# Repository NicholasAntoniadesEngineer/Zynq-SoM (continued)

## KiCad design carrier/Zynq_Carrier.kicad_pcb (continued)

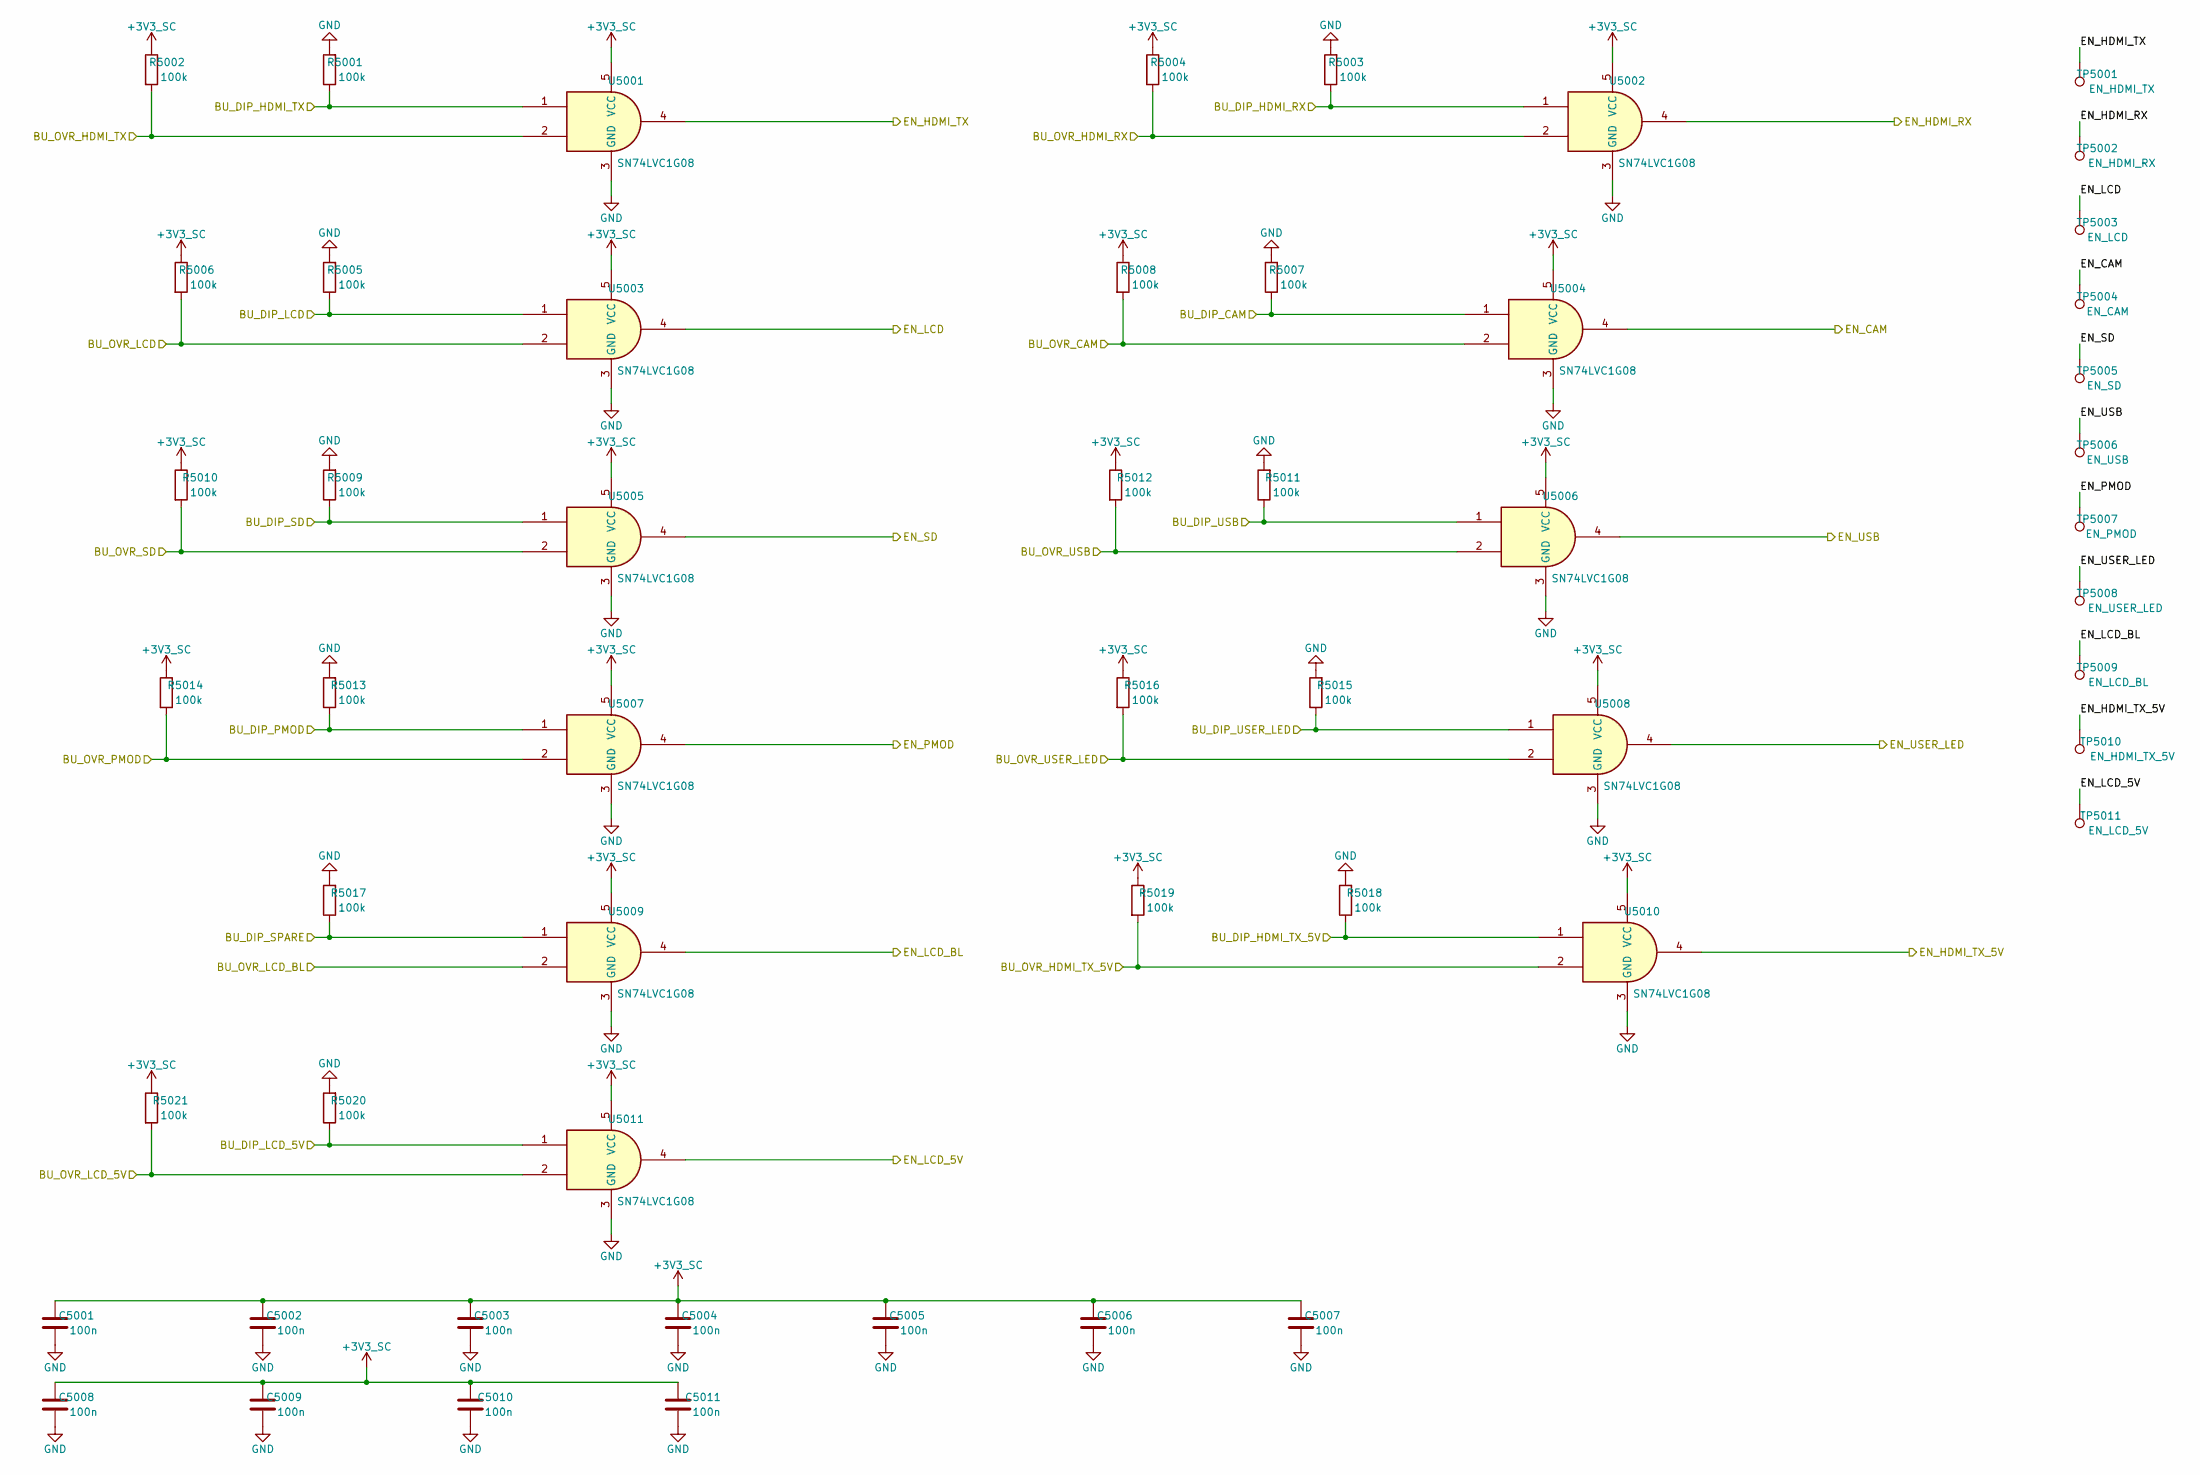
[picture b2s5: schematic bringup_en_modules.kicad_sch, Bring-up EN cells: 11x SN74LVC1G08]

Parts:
C5001, C5002, C5003, C5004, C5005, C5006, C5007, C5008, C5009, C5010, C5011: 100n; C_0603_1608Metric; LCSC C14663
R5001, R5002, R5003, R5004, R5005, R5006, R5007, R5008, R5009, R5010, R5011, R5012, R5013, R5014, R5015, R5016, R5017, R5018, R5019, R5020, R5021: 100k; R_0603_1608Metric; LCSC C25803
TP5001: EN_HDMI_TX; TestPoint_Pad_D1.5mm
TP5002: EN_HDMI_RX; TestPoint_Pad_D1.5mm
TP5003: EN_LCD; TestPoint_Pad_D1.5mm
TP5004: EN_CAM; TestPoint_Pad_D1.5mm
TP5005: EN_SD; TestPoint_Pad_D1.5mm
TP5006: EN_USB; TestPoint_Pad_D1.5mm
TP5007: EN_PMOD; TestPoint_Pad_D1.5mm
TP5008: EN_USER_LED; TestPoint_Pad_D1.5mm
TP5009: EN_LCD_BL; TestPoint_Pad_D1.5mm
TP5010: EN_HDMI_TX_5V; TestPoint_Pad_D1.5mm
TP5011: EN_LCD_5V; TestPoint_Pad_D1.5mm
U5001, U5002, U5003, U5004, U5005, U5006, U5007, U5008, U5009, U5010, U5011: SN74LVC1G08; SOT-23-5; LCSC C7666

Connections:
+3V3_SC: C5001.1, C5002.1, C5003.1, C5004.1, C5005.1, C5006.1, C5007.1, C5008.1, C5009.1, C5010.1, C5011.1, R5002.1, R5004.1, R5006.1, R5008.1, R5010.1, R5012.1, R5014.1, R5016.1, R5019.1, R5021.1, U5001.5 (VCC), U5002.5 (VCC), U5003.5 (VCC), U5004.5 (VCC), U5005.5 (VCC), U5006.5 (VCC), U5007.5 (VCC), U5008.5 (VCC), U5009.5 (VCC), U5010.5 (VCC), U5011.5 (VCC); also elsewhere on the board
BU_DIP_CAM: R5007.1, U5004.1; also elsewhere on the board
BU_DIP_HDMI_RX: R5003.1, U5002.1; also elsewhere on the board
BU_DIP_HDMI_TX: R5001.1, U5001.1; also elsewhere on the board
BU_DIP_HDMI_TX_5V: R5018.1, U5010.1; also elsewhere on the board
BU_DIP_LCD: R5005.1, U5003.1; also elsewhere on the board
BU_DIP_LCD_5V: R5020.1, U5011.1; also elsewhere on the board
BU_DIP_PMOD: R5013.1, U5007.1; also elsewhere on the board
BU_DIP_SD: R5009.1, U5005.1; also elsewhere on the board
BU_DIP_SPARE: R5017.1, U5009.1; also elsewhere on the board
BU_DIP_USB: R5011.1, U5006.1; also elsewhere on the board
BU_DIP_USER_LED: R5015.1, U5008.1; also elsewhere on the board
BU_OVR_CAM: R5008.2, U5004.2; also elsewhere on the board
BU_OVR_HDMI_RX: R5004.2, U5002.2; also elsewhere on the board
BU_OVR_HDMI_TX: R5002.2, U5001.2; also elsewhere on the board
BU_OVR_HDMI_TX_5V: R5019.2, U5010.2; also elsewhere on the board
BU_OVR_LCD: R5006.2, U5003.2; also elsewhere on the board
BU_OVR_LCD_5V: R5021.2, U5011.2; also elsewhere on the board
BU_OVR_LCD_BL: U5009.2; also elsewhere on the board
BU_OVR_PMOD: R5014.2, U5007.2; also elsewhere on the board
BU_OVR_SD: R5010.2, U5005.2; also elsewhere on the board
BU_OVR_USB: R5012.2, U5006.2; also elsewhere on the board
BU_OVR_USER_LED: R5016.2, U5008.2; also elsewhere on the board
EN_CAM: TP5004.1, U5004.4; also elsewhere on the board
EN_HDMI_RX: TP5002.1, U5002.4; also elsewhere on the board
EN_HDMI_TX: TP5001.1, U5001.4; also elsewhere on the board
EN_HDMI_TX_5V: TP5010.1, U5010.4; also elsewhere on the board
EN_LCD: TP5003.1, U5003.4; also elsewhere on the board
EN_LCD_5V: TP5011.1, U5011.4; also elsewhere on the board
EN_LCD_BL: TP5009.1, U5009.4
EN_PMOD: TP5007.1, U5007.4; also elsewhere on the board
EN_SD: TP5005.1, U5005.4; also elsewhere on the board
EN_USB: TP5006.1, U5006.4; also elsewhere on the board
EN_USER_LED: TP5008.1, U5008.4; also elsewhere on the board
GND: C5001.2, C5002.2, C5003.2, C5004.2, C5005.2, C5006.2, C5007.2, C5008.2, C5009.2, C5010.2, C5011.2, R5001.2, R5003.2, R5005.2, R5007.2, R5009.2, R5011.2, R5013.2, R5015.2, R5017.2, R5018.2, R5020.2, U5001.3 (GND), U5002.3 (GND), U5003.3 (GND), U5004.3 (GND), U5005.3 (GND), U5006.3 (GND), U5007.3 (GND), U5008.3 (GND), U5009.3 (GND), U5010.3 (GND), U5011.3 (GND); also elsewhere on the board

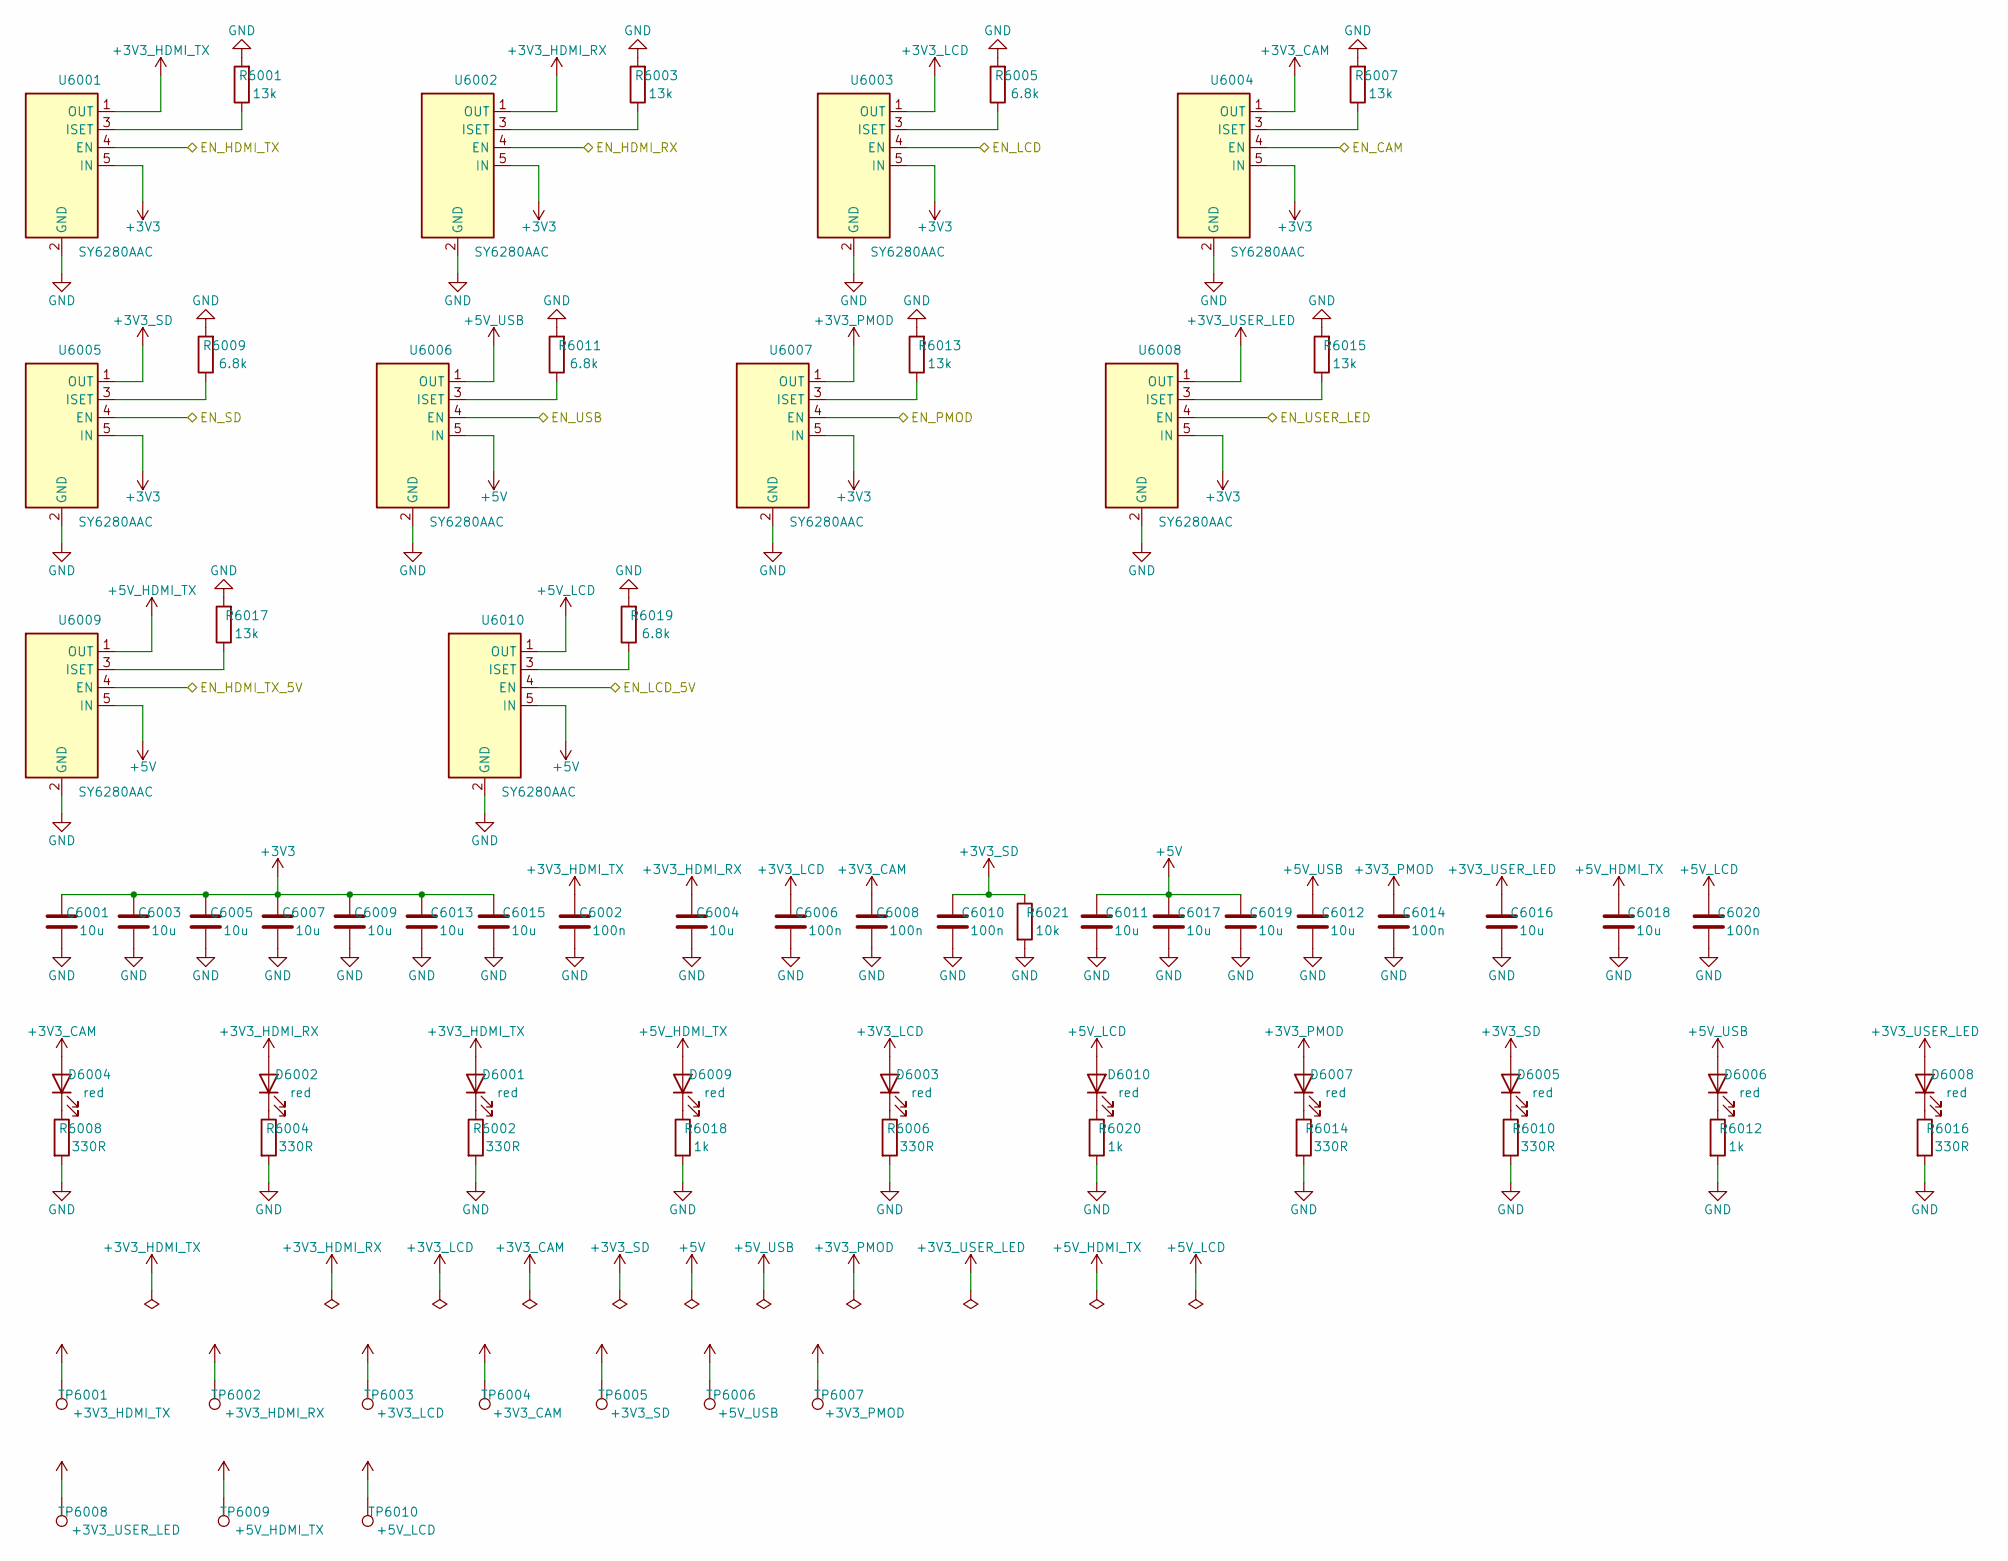
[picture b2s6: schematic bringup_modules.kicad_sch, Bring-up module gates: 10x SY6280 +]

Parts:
C6001, C6003, C6004, C6005, C6007, C6009, C6011, C6012, C6013, C6015, C6016, C6017, C6018, C6019: 10u; C_0805_2012Metric; LCSC C15850
C6002, C6006, C6008, C6010, C6014, C6020: 100n; C_0603_1608Metric; LCSC C14663
D6001, D6002, D6003, D6004, D6005, D6006, D6007, D6008, D6009, D6010: red; LED_0603_1608Metric; LCSC C2286
R6001, R6003, R6007, R6013, R6015, R6017: 13k; R_0603_1608Metric; LCSC C22797
R6002, R6004, R6006, R6008, R6010, R6014, R6016: 330R; R_0603_1608Metric; LCSC C23138
R6005, R6009, R6011, R6019: 6.8k; R_0603_1608Metric; LCSC C23212
R6012, R6018, R6020: 1k; R_0603_1608Metric; LCSC C21190
R6021: 10k; R_0603_1608Metric; LCSC C25804
TP6001: +3V3_HDMI_TX; TestPoint_Pad_D1.5mm
TP6002: +3V3_HDMI_RX; TestPoint_Pad_D1.5mm
TP6003: +3V3_LCD; TestPoint_Pad_D1.5mm
TP6004: +3V3_CAM; TestPoint_Pad_D1.5mm
TP6005: +3V3_SD; TestPoint_Pad_D1.5mm
TP6006: +5V_USB; TestPoint_Pad_D1.5mm
TP6007: +3V3_PMOD; TestPoint_Pad_D1.5mm
TP6008: +3V3_USER_LED; TestPoint_Pad_D1.5mm
TP6009: +5V_HDMI_TX; TestPoint_Pad_D1.5mm
TP6010: +5V_LCD; TestPoint_Pad_D1.5mm
U6001, U6002, U6003, U6004, U6005, U6006, U6007, U6008, U6009, U6010: SY6280AAC; LCSC C55136

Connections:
+3V3: C6001.1, C6003.1, C6005.1, C6007.1, C6009.1, C6013.1, C6015.1, U6001.5 (IN), U6002.5 (IN), U6003.5 (IN), U6004.5 (IN), U6005.5 (IN), U6007.5 (IN), U6008.5 (IN); also elsewhere on the board
+3V3_CAM: C6008.1, D6004.2 (A), TP6004.1, U6004.1 (OUT); also elsewhere on the board
+3V3_HDMI_RX: C6004.1, D6002.2 (A), TP6002.1, U6002.1 (OUT); also elsewhere on the board
+3V3_HDMI_TX: C6002.1, D6001.2 (A), TP6001.1, U6001.1 (OUT); also elsewhere on the board
+3V3_LCD: C6006.1, D6003.2 (A), TP6003.1, U6003.1 (OUT); also elsewhere on the board
+3V3_PMOD: C6014.1, D6007.2 (A), TP6007.1, U6007.1 (OUT); also elsewhere on the board
+3V3_SD: C6010.1, D6005.2 (A), R6021.1, TP6005.1, U6005.1 (OUT); also elsewhere on the board
+3V3_USER_LED: C6016.1, D6008.2 (A), TP6008.1, U6008.1 (OUT); also elsewhere on the board
+5V: C6011.1, C6017.1, C6019.1, U6006.5 (IN), U6009.5 (IN), U6010.5 (IN); also elsewhere on the board
+5V_HDMI_TX: C6018.1, D6009.2 (A), TP6009.1, U6009.1 (OUT); also elsewhere on the board
+5V_LCD: C6020.1, D6010.2 (A), TP6010.1, U6010.1 (OUT); also elsewhere on the board
+5V_USB: C6012.1, D6006.2 (A), TP6006.1, U6006.1 (OUT); also elsewhere on the board
EN_CAM: U6004.4 (EN); also elsewhere on the board
EN_HDMI_RX: U6002.4 (EN); also elsewhere on the board
EN_HDMI_TX: U6001.4 (EN); also elsewhere on the board
EN_HDMI_TX_5V: U6009.4 (EN); also elsewhere on the board
EN_LCD: U6003.4 (EN); also elsewhere on the board
EN_LCD_5V: U6010.4 (EN); also elsewhere on the board
EN_PMOD: U6007.4 (EN); also elsewhere on the board
EN_SD: U6005.4 (EN); also elsewhere on the board
EN_USB: U6006.4 (EN); also elsewhere on the board
EN_USER_LED: U6008.4 (EN); also elsewhere on the board
GND: C6001.2, C6002.2, C6003.2, C6004.2, C6005.2, C6006.2, C6007.2, C6008.2, C6009.2, C6010.2, C6011.2, C6012.2, C6013.2, C6014.2, C6015.2, C6016.2, C6017.2, C6018.2, C6019.2, C6020.2, R6001.2, R6002.2, R6003.2, R6004.2, R6005.2, R6006.2, R6007.2, R6008.2, R6009.2, R6010.2, R6011.2, R6012.2, R6013.2, R6014.2, R6015.2, R6016.2, R6017.2, R6018.2, R6019.2, R6020.2, R6021.2, U6001.2 (GND), U6002.2 (GND), U6003.2 (GND), U6004.2 (GND), U6005.2 (GND), U6006.2 (GND), U6007.2 (GND), U6008.2 (GND), U6009.2 (GND), U6010.2 (GND); also elsewhere on the board
unnamed: D6001.1 (K), R6002.1
unnamed: D6002.1 (K), R6004.1
unnamed: D6003.1 (K), R6006.1
unnamed: D6004.1 (K), R6008.1
unnamed: D6005.1 (K), R6010.1
unnamed: D6006.1 (K), R6012.1
unnamed: D6007.1 (K), R6014.1
unnamed: D6008.1 (K), R6016.1
unnamed: D6009.1 (K), R6018.1
unnamed: D6010.1 (K), R6020.1
unnamed: R6001.1, U6001.3 (ISET)
unnamed: R6003.1, U6002.3 (ISET)
unnamed: R6005.1, U6003.3 (ISET)
unnamed: R6007.1, U6004.3 (ISET)
unnamed: R6009.1, U6005.3 (ISET)
unnamed: R6011.1, U6006.3 (ISET)
unnamed: R6013.1, U6007.3 (ISET)
unnamed: R6015.1, U6008.3 (ISET)
unnamed: R6017.1, U6009.3 (ISET)
unnamed: R6019.1, U6010.3 (ISET)

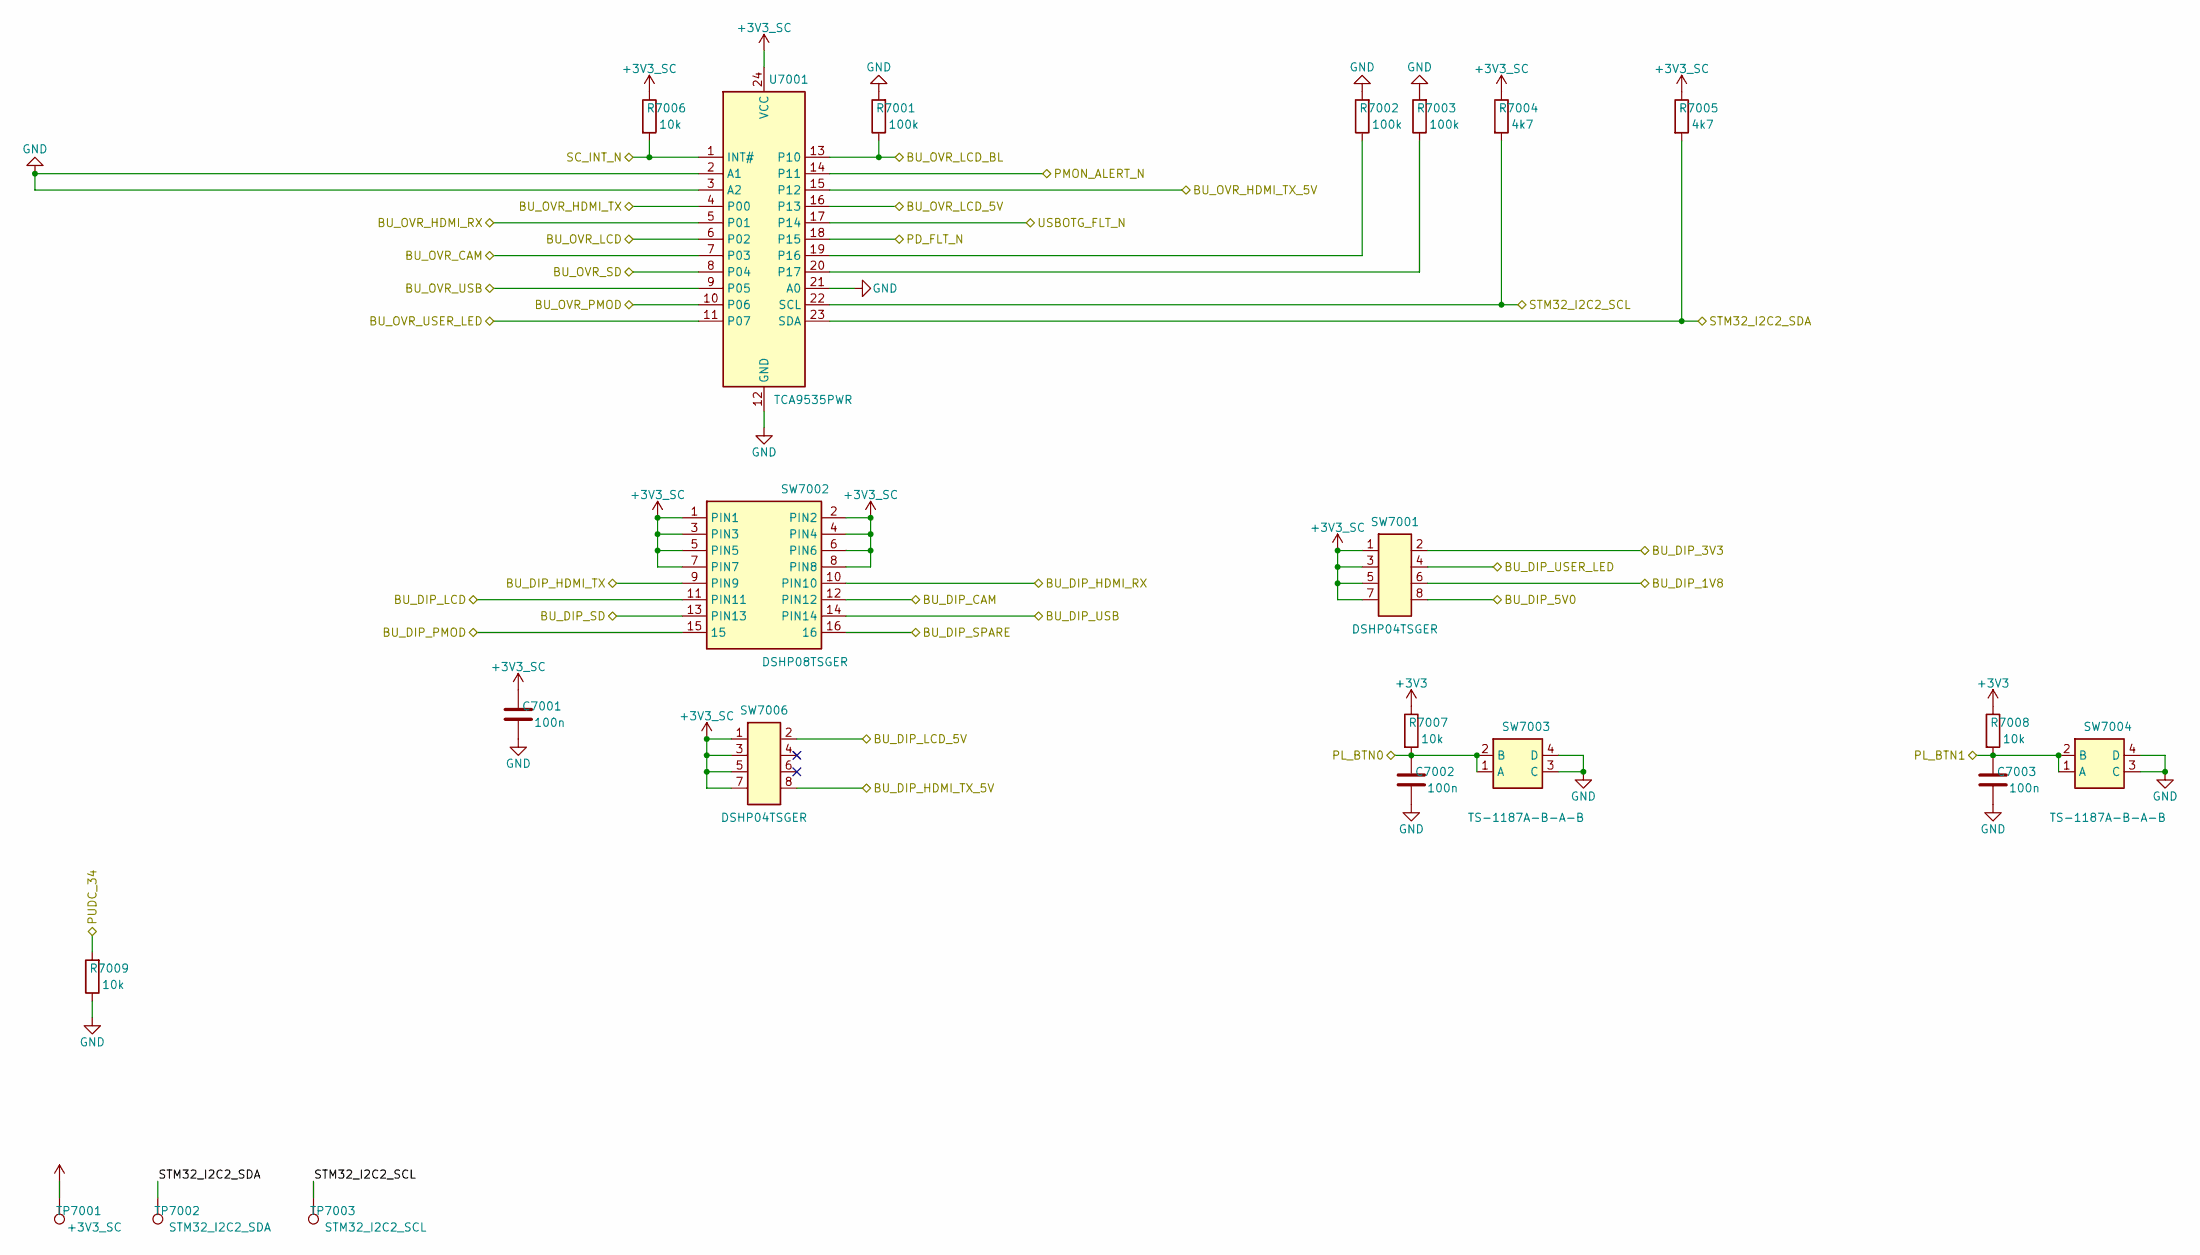
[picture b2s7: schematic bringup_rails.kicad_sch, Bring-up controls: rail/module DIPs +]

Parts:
C7001, C7002, C7003: 100n; C_0603_1608Metric; LCSC C14663
R7001, R7002, R7003: 100k; R_0603_1608Metric; LCSC C25803
R7004, R7005: 4k7; R_0603_1608Metric; LCSC C23162
R7006, R7007, R7008, R7009: 10k; R_0603_1608Metric; LCSC C25804
SW7001, SW7006: DSHP04TSGER; LCSC C3293144
SW7002: DSHP08TSGER; LCSC C3293147
SW7003, SW7004: TS-1187A-B-A-B; LCSC C318884
TP7001: +3V3_SC; TestPoint_Pad_D1.5mm
TP7002: STM32_I2C2_SDA; TestPoint_Pad_D1.5mm
TP7003: STM32_I2C2_SCL; TestPoint_Pad_D1.5mm
U7001: TCA9535PWR; LCSC C130204

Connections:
+3V3: R7007.1, R7008.1; also elsewhere on the board
+3V3_SC: C7001.1, R7004.1, R7005.1, R7006.1, SW7001.1, SW7001.3, SW7001.5, SW7001.7, SW7002.1 (PIN1), SW7002.2 (PIN2), SW7002.3 (PIN3), SW7002.4 (PIN4), SW7002.5 (PIN5), SW7002.6 (PIN6), SW7002.7 (PIN7), SW7002.8 (PIN8), SW7006.1, SW7006.3, SW7006.5, SW7006.7, TP7001.1, U7001.24 (VCC); also elsewhere on the board
BU_DIP_1V8: SW7001.6; also elsewhere on the board
BU_DIP_3V3: SW7001.2; also elsewhere on the board
BU_DIP_5V0: SW7001.8; also elsewhere on the board
BU_DIP_CAM: SW7002.12 (PIN12); also elsewhere on the board
BU_DIP_HDMI_RX: SW7002.10 (PIN10); also elsewhere on the board
BU_DIP_HDMI_TX: SW7002.9 (PIN9); also elsewhere on the board
BU_DIP_HDMI_TX_5V: SW7006.8; also elsewhere on the board
BU_DIP_LCD: SW7002.11 (PIN11); also elsewhere on the board
BU_DIP_LCD_5V: SW7006.2; also elsewhere on the board
BU_DIP_PMOD: SW7002.15; also elsewhere on the board
BU_DIP_SD: SW7002.13 (PIN13); also elsewhere on the board
BU_DIP_SPARE: SW7002.16; also elsewhere on the board
BU_DIP_USB: SW7002.14 (PIN14); also elsewhere on the board
BU_DIP_USER_LED: SW7001.4; also elsewhere on the board
BU_OVR_CAM: U7001.7 (P03); also elsewhere on the board
BU_OVR_HDMI_RX: U7001.5 (P01); also elsewhere on the board
BU_OVR_HDMI_TX: U7001.4 (P00); also elsewhere on the board
BU_OVR_HDMI_TX_5V: U7001.15 (P12); also elsewhere on the board
BU_OVR_LCD: U7001.6 (P02); also elsewhere on the board
BU_OVR_LCD_5V: U7001.16 (P13); also elsewhere on the board
BU_OVR_LCD_BL: R7001.1, U7001.13 (P10); also elsewhere on the board
BU_OVR_PMOD: U7001.10 (P06); also elsewhere on the board
BU_OVR_SD: U7001.8 (P04); also elsewhere on the board
BU_OVR_USB: U7001.9 (P05); also elsewhere on the board
BU_OVR_USER_LED: U7001.11 (P07); also elsewhere on the board
GND: C7001.2, C7002.2, C7003.2, R7001.2, R7002.2, R7003.2, R7009.1, SW7003.3 (C), SW7003.4 (D), SW7004.3 (C), SW7004.4 (D), U7001.2 (A1), U7001.3 (A2), U7001.12 (GND), U7001.21 (A0); also elsewhere on the board
unnamed: R7002.1, U7001.19 (P16)
unnamed: R7003.1, U7001.20 (P17)
PD_FLT_N: U7001.18 (P15); also elsewhere on the board
PL_BTN0: C7002.1, R7007.2, SW7003.1 (A), SW7003.2 (B); also elsewhere on the board
PL_BTN1: C7003.1, R7008.2, SW7004.1 (A), SW7004.2 (B); also elsewhere on the board
PMON_ALERT_N: U7001.14 (P11); also elsewhere on the board
PUDC_34: R7009.2; also elsewhere on the board
SC_INT_N: R7006.2, U7001.1 (INT#); also elsewhere on the board
STM32_I2C2_SCL: R7004.2, TP7003.1, U7001.22 (SCL); also elsewhere on the board
STM32_I2C2_SDA: R7005.2, TP7002.1, U7001.23 (SDA); also elsewhere on the board
USBOTG_FLT_N: U7001.17 (P14); also elsewhere on the board

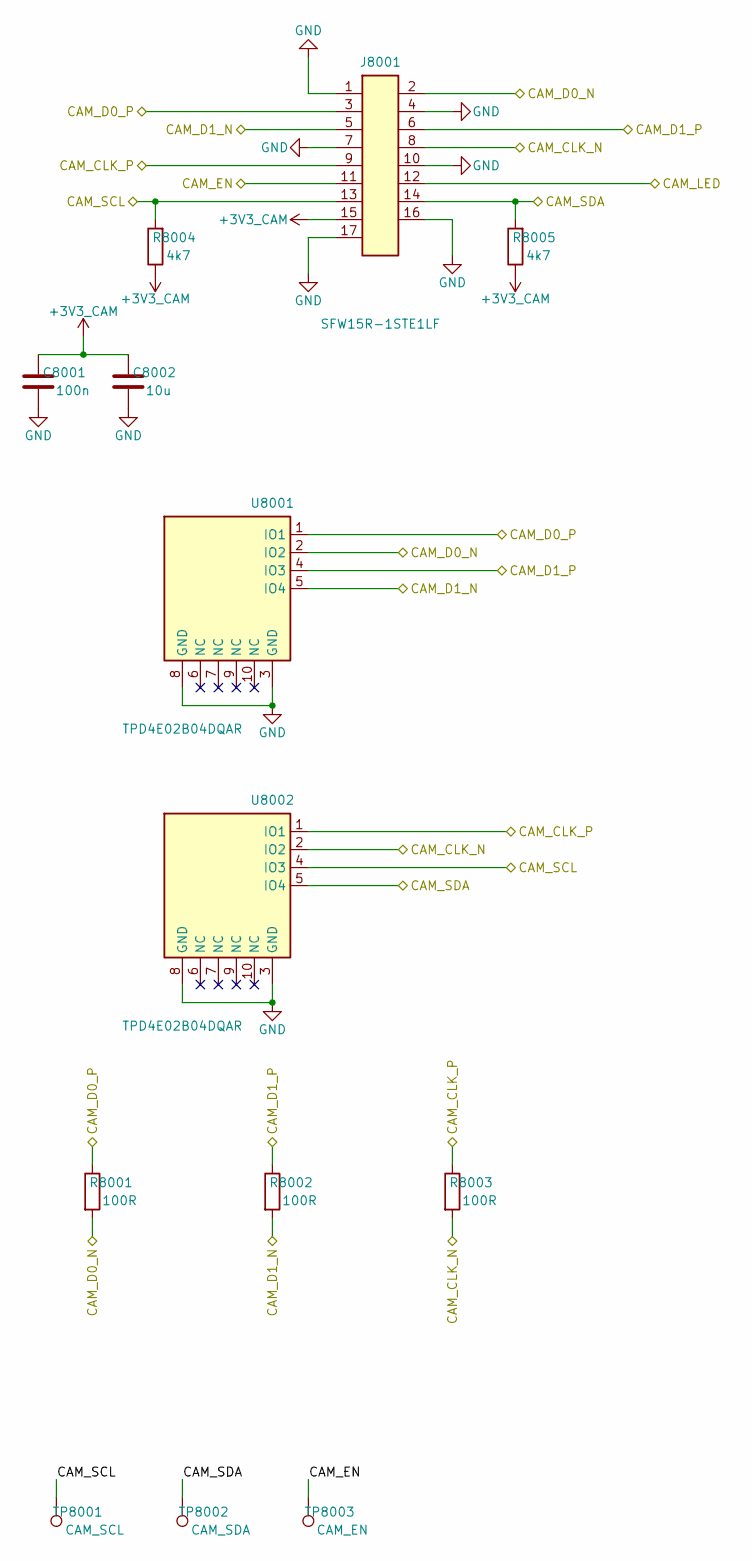
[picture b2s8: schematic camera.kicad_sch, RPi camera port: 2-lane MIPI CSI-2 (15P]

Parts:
C8001: 100n; C_0603_1608Metric; LCSC C14663
C8002: 10u; C_0805_2012Metric; LCSC C15850
J8001: SFW15R-1STE1LF; LCSC C3168538
R8001, R8002, R8003: 100R; R_0603_1608Metric; LCSC C22775
R8004, R8005: 4k7; R_0603_1608Metric; LCSC C23162
TP8001: CAM_SCL; TestPoint_Pad_D1.5mm
TP8002: CAM_SDA; TestPoint_Pad_D1.5mm
TP8003: CAM_EN; TestPoint_Pad_D1.5mm
U8001, U8002: TPD4E02B04DQAR; LCSC C106794

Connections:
+3V3_CAM: C8001.1, C8002.1, J8001.15, R8004.1, R8005.1; also elsewhere on the board
CAM_CLK_N: J8001.8, R8003.2, U8002.2 (IO2); also elsewhere on the board
CAM_CLK_P: J8001.9, R8003.1, U8002.1 (IO1); also elsewhere on the board
CAM_D0_N: J8001.2, R8001.2, U8001.2 (IO2); also elsewhere on the board
CAM_D0_P: J8001.3, R8001.1, U8001.1 (IO1); also elsewhere on the board
CAM_D1_N: J8001.5, R8002.2, U8001.5 (IO4); also elsewhere on the board
CAM_D1_P: J8001.6, R8002.1, U8001.4 (IO3); also elsewhere on the board
CAM_EN: J8001.11, TP8003.1; also elsewhere on the board
CAM_LED: J8001.12; also elsewhere on the board
CAM_SCL: J8001.13, R8004.2, TP8001.1, U8002.4 (IO3); also elsewhere on the board
CAM_SDA: J8001.14, R8005.2, TP8002.1, U8002.5 (IO4); also elsewhere on the board
GND: C8001.2, C8002.2, J8001.1, J8001.4, J8001.7, J8001.10, J8001.16, J8001.17, U8001.3 (GND), U8001.8 (GND), U8002.3 (GND), U8002.8 (GND); also elsewhere on the board

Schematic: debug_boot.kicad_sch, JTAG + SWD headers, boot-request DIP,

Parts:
J9001: 878311420; LCSC C240854
J9002: HX_JN1.27-2x5; HX_JN1.27-2x5_TP_H4.9; LCSC C42372555
R9001, R9002: 4k7; R_0603_1608Metric; LCSC C23162
R9003: 100R; R_0603_1608Metric; LCSC C22775
R9004, R9005, R9006: 10k; R_0603_1608Metric; LCSC C25804
SW9001: DIP-4; DSHP04TSGER; LCSC C3293144
SW9002: RESET; TS-1187A-B-A-B; LCSC C318884

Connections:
+3V3: J9001.2, R9001.1, R9002.1; also elsewhere on the board
+3V3_SC: J9002.1, R9003.1, R9004.1, R9005.1, R9006.1; also elsewhere on the board
GND: J9001.1, J9001.3, J9001.5, J9001.7, J9001.9, J9001.11, J9001.13, J9002.3, J9002.5, J9002.9, SW9001.5, SW9001.6, SW9001.7, SW9002.3 (C), SW9002.4 (D); also elsewhere on the board
unnamed: R9003.2, SW9001.8
unnamed: R9006.2, SW9001.4
STM32_BOOT0: SW9001.1; also elsewhere on the board
STM32_GPIO5: J9002.4; also elsewhere on the board
STM32_GPIO6: J9002.2; also elsewhere on the board
STM32_GPIO7: R9004.2, SW9001.2; also elsewhere on the board
STM32_GPIO8: R9005.2, SW9001.3; also elsewhere on the board
STM32_NRST: J9002.10, SW9002.1 (A), SW9002.2 (B); also elsewhere on the board
ZYNQ_TCK: J9001.6; also elsewhere on the board
ZYNQ_TDI: J9001.10, R9002.2; also elsewhere on the board
ZYNQ_TDO: J9001.8; also elsewhere on the board
ZYNQ_TMS: J9001.4, R9001.2; also elsewhere on the board

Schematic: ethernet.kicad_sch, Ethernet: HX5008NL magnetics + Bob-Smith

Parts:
C10001, C10002, C10003, C10004, C10005: 1n; C_1206_3225Metric; LCSC C9196
C10006: 100n; C_0603_1608Metric; LCSC C14663
R10001, R10002, R10003, R10004: 75R; R_0603_1608Metric; LCSC C4275
T10001: HX5008NLT; LCSC C962544

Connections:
/ethernet/BS_COMMON: C10001.2, C10002.2, C10003.2, C10004.2, C10005.1, R10001.2, R10002.2, R10003.2, R10004.2
/ethernet/ETH_TCT: C10006.1, T10001.1 (TCT1), T10001.4 (TCT2), T10001.7 (TCT3), T10001.10 (TCT4)
/ethernet/MCT1: C10001.1, R10001.1, T10001.24 (MCT1)
/ethernet/MCT2: C10002.1, R10002.1, T10001.21 (MCT2)
/ethernet/MCT3: C10003.1, R10003.1, T10001.18 (MCT3)
/ethernet/MCT4: C10004.1, R10004.1, T10001.15 (MCT4)
CHASSIS_GND: C10005.2; also elsewhere on the board
ETH_LINE_MDI_0_N: T10001.22 (MX1-); also elsewhere on the board
ETH_LINE_MDI_0_P: T10001.23 (MX1+); also elsewhere on the board
ETH_LINE_MDI_1_N: T10001.19 (MX2-); also elsewhere on the board
ETH_LINE_MDI_1_P: T10001.20 (MX2+); also elsewhere on the board
ETH_LINE_MDI_2_N: T10001.16 (MX3-); also elsewhere on the board
ETH_LINE_MDI_2_P: T10001.17 (MX3+); also elsewhere on the board
ETH_LINE_MDI_3_N: T10001.13 (MX4-); also elsewhere on the board
ETH_LINE_MDI_3_P: T10001.14 (MX4+); also elsewhere on the board
ETH_PHY_MDI0_N: T10001.3 (TD1-); also elsewhere on the board
ETH_PHY_MDI0_P: T10001.2 (TD1+); also elsewhere on the board
ETH_PHY_MDI1_N: T10001.6 (TD2-); also elsewhere on the board
ETH_PHY_MDI1_P: T10001.5 (TD2+); also elsewhere on the board
ETH_PHY_MDI2_N: T10001.9 (TD3-); also elsewhere on the board
ETH_PHY_MDI2_P: T10001.8 (TD3+); also elsewhere on the board
ETH_PHY_MDI3_N: T10001.12 (TD4-); also elsewhere on the board
ETH_PHY_MDI3_P: T10001.11 (TD4+); also elsewhere on the board
GND: C10006.2; also elsewhere on the board

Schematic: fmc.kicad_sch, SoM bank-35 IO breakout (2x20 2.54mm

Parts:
C11001, C11004: 10u; C_0805_2012Metric; LCSC C15850
C11002, C11005: 100n; C_0603_1608Metric; LCSC C14663
C11003: 1u; C_0603_1608Metric; LCSC C15849
J11001: Header_2x20_2.54mm; PinHeader_2x20_P2.54mm_Vertical; LCSC C50980
TP11001: +2V5_VADJ; TestPoint_Pad_D1.5mm
U11001: TLV75725PDYDR; LCSC C35209004

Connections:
+2V5_VADJ: C11004.1, C11005.1, J11001.2, TP11001.1, U11001.5 (OUT); also elsewhere on the board
+3V3: C11001.1, C11002.1, C11003.1, J11001.1, U11001.1 (IN), U11001.3 (EN); also elsewhere on the board
FMC_CLK0_M2C_N: J11001.4; also elsewhere on the board
FMC_CLK0_M2C_P: J11001.3; also elsewhere on the board
FMC_CLK1_M2C_N: J11001.6; also elsewhere on the board
FMC_CLK1_M2C_P: J11001.5; also elsewhere on the board
FMC_LA00_CC_N: J11001.10; also elsewhere on the board
FMC_LA00_CC_P: J11001.9; also elsewhere on the board
FMC_LA01_CC_N: J11001.12; also elsewhere on the board
FMC_LA01_CC_P: J11001.11; also elsewhere on the board
FMC_LA02_N: J11001.14; also elsewhere on the board
FMC_LA02_P: J11001.13; also elsewhere on the board
FMC_LA03_N: J11001.18; also elsewhere on the board
FMC_LA03_P: J11001.17; also elsewhere on the board
FMC_LA04_N: J11001.20; also elsewhere on the board
FMC_LA04_P: J11001.19; also elsewhere on the board
FMC_LA05_N: J11001.22; also elsewhere on the board
FMC_LA05_P: J11001.21; also elsewhere on the board
FMC_LA06_N: J11001.26; also elsewhere on the board
FMC_LA06_P: J11001.25; also elsewhere on the board
FMC_LA07_N: J11001.28; also elsewhere on the board
FMC_LA07_P: J11001.27; also elsewhere on the board
FMC_LA08_N: J11001.30; also elsewhere on the board
FMC_LA08_P: J11001.29; also elsewhere on the board
FMC_LA09_N: J11001.34; also elsewhere on the board
FMC_LA09_P: J11001.33; also elsewhere on the board
FMC_LA10_N: J11001.36; also elsewhere on the board
FMC_LA10_P: J11001.35; also elsewhere on the board
FMC_LA11_N: J11001.38; also elsewhere on the board
FMC_LA11_P: J11001.37; also elsewhere on the board
GND: C11001.2, C11002.2, C11003.2, C11004.2, C11005.2, J11001.7, J11001.8, J11001.15, J11001.16, J11001.23, J11001.24, J11001.31, J11001.32, J11001.39, J11001.40, U11001.2 (GND), U11001.6 (EP); also elsewhere on the board

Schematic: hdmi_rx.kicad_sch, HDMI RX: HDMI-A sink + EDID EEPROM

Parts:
C12001: 100n; C_0603_1608Metric; LCSC C14663
J12001: HDMI-019S; LCSC C111617
R12001: 1k; R_0603_1608Metric; LCSC C21190
R12002: 27k; R_0603_1608Metric; LCSC C22967
R12003: 10k; R_0603_1608Metric; LCSC C25804
R12004: 15k; R_0603_1608Metric; LCSC C22809
U12001: M24C02-WMN6TP; MPN M24C02-WMN6TP; LCSC C7562
U12002, U12003: TPD4E02B04DQAR; LCSC C106794
U12004: TPD4E05U06DQAR; LCSC C138714

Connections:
+3V3_HDMI_RX: R12002.1; also elsewhere on the board
/hdmi_rx/HDMI_RX_5V: C12001.1, J12001.18 (+5V), R12001.1, R12003.1, U12001.7 (~WC), U12001.8 (VCC)
/hdmi_rx/HDMI_RX_HPD: J12001.19 (HOT_PLUG_DET), R12001.2, U12004.5 (D2-)
/hdmi_rx/HDMI_RX_SCL: J12001.15 (I2C-CLK), U12001.6 (SCL), U12004.1 (D1+)
/hdmi_rx/HDMI_RX_SDA: J12001.16 (I2C_DATA), U12001.5 (SDA), U12004.2 (D1-)
CHASSIS_GND: J12001.20 (SHD), J12001.21 (SHD), J12001.22 (SHD), J12001.23 (SHD); also elsewhere on the board
GND: C12001.2, J12001.2 (D2_SHIELD), J12001.5 (D1_SHIELD), J12001.8 (D0_SHIELD), J12001.11 (CK_SHIELD), J12001.17 (GND), R12004.2, U12001.1 (E0), U12001.2 (E1), U12001.3 (E2), U12001.4 (VSS), U12002.3 (GND), U12002.8 (GND), U12003.3 (GND), U12003.8 (GND), U12004.3 (GND), U12004.8 (GND); also elsewhere on the board
HDMI_RX_5V_DET: R12003.2, R12004.1; also elsewhere on the board
HDMI_RX_CEC: J12001.13 (CEC), R12002.2, U12004.4 (D2+); also elsewhere on the board
HDMI_RX_CLK_N: J12001.12 (CK-), U12003.5 (IO4); also elsewhere on the board
HDMI_RX_CLK_P: J12001.10 (CK+), U12003.4 (IO3); also elsewhere on the board
HDMI_RX_D0_N: J12001.9 (D0-), U12003.2 (IO2); also elsewhere on the board
HDMI_RX_D0_P: J12001.7 (D0+), U12003.1 (IO1); also elsewhere on the board
HDMI_RX_D1_N: J12001.6 (D1-), U12002.5 (IO4); also elsewhere on the board
HDMI_RX_D1_P: J12001.4 (D1+), U12002.4 (IO3); also elsewhere on the board
HDMI_RX_D2_N: J12001.3 (D2-), U12002.2 (IO2); also elsewhere on the board
HDMI_RX_D2_P: J12001.1 (D2+), U12002.1 (IO1); also elsewhere on the board

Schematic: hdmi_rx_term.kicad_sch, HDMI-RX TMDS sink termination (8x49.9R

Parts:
C13001: 100n; C_0603_1608Metric; LCSC C14663
C13002: 1u; C_0603_1608Metric; LCSC C15849
R13001, R13002, R13003, R13004, R13005, R13006, R13007, R13008: 49.9R; R_0603_1608Metric; LCSC C114625

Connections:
+3V3: C13001.1, C13002.1, R13001.2, R13002.2, R13003.2, R13004.2, R13005.2, R13006.2, R13007.2, R13008.2; also elsewhere on the board
GND: C13001.2, C13002.2; also elsewhere on the board
HDMI_RX_CLK_N: R13008.1; also elsewhere on the board
HDMI_RX_CLK_P: R13007.1; also elsewhere on the board
HDMI_RX_D0_N: R13006.1; also elsewhere on the board
HDMI_RX_D0_P: R13005.1; also elsewhere on the board
HDMI_RX_D1_N: R13004.1; also elsewhere on the board
HDMI_RX_D1_P: R13003.1; also elsewhere on the board
HDMI_RX_D2_N: R13002.1; also elsewhere on the board
HDMI_RX_D2_P: R13001.1; also elsewhere on the board
